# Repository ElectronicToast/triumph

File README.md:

Analog function generator project for EE 90 at Caltech

## Description

The Triumph Analog Function Generator is an analog function generator constructed for the Analog Electronics Project Laboratory (EE 90) capstone course at Caltech. It provides a single output channel on a 50 Ω impedance matched BNC connector. It is capable of producing sine, square, and triangle waveforms that vary in frequency over at least the range 10 Hz to 20 kHz, in addition to DC. The frequency may be adjusted through the combination of a frequency range select switch and a fine-adjustment knob on the top of the device. The output amplitude may be varied from zero up to 10 V (single-sided)  with a control knob. A second control knob allows the DC offset of the output to be varied. 

Power is supplied via 9 – 18 VDC input through a barrel jack connector on the rear of the device. A rocker switch near the power connector allows the device to be switched on and off.

A blue indicator LED on the front of the device indicates if the function generator is powered.

## Photos

## Design

An integrator with Schmitt feedback is used to generate a base triangle wave, which is passed to a Middlebrook-Richer JFET converter to create a sine wave and also a comparator to create a square wave. A positive feedback circuit associated to the comparator provides square wave duty cycle control. A final output stage provides amplitude and offset control. This general architecture achieves a good balance among simplicity, reliability, and performance.

The electronics were split among two PCBs: a main board with the function generator circuitry, and a power board that functions as a DC-DC converter supplying the former with a dual polarity power supply.

The electronics were designed with KiCad EDA v. 5.1.2. The `/triumph-main` directory contains files, documentation, and fabrication output for the main board, while the `/triumph-main-production` directory contains files reflecting post-fabrication design changes. The `/triumph-power` directory contains files for the power board.

The enclosure was designed with SolidWorks 2018, CorelDraw X7, and the [MakerCase](https://en.makercase.com/) box generator.

## Author
- Ray Sun - Undergraduate, Electrical Engineering, Caltech, Class of 2020

## Licensing
This project is released under the terms of the MIT License.

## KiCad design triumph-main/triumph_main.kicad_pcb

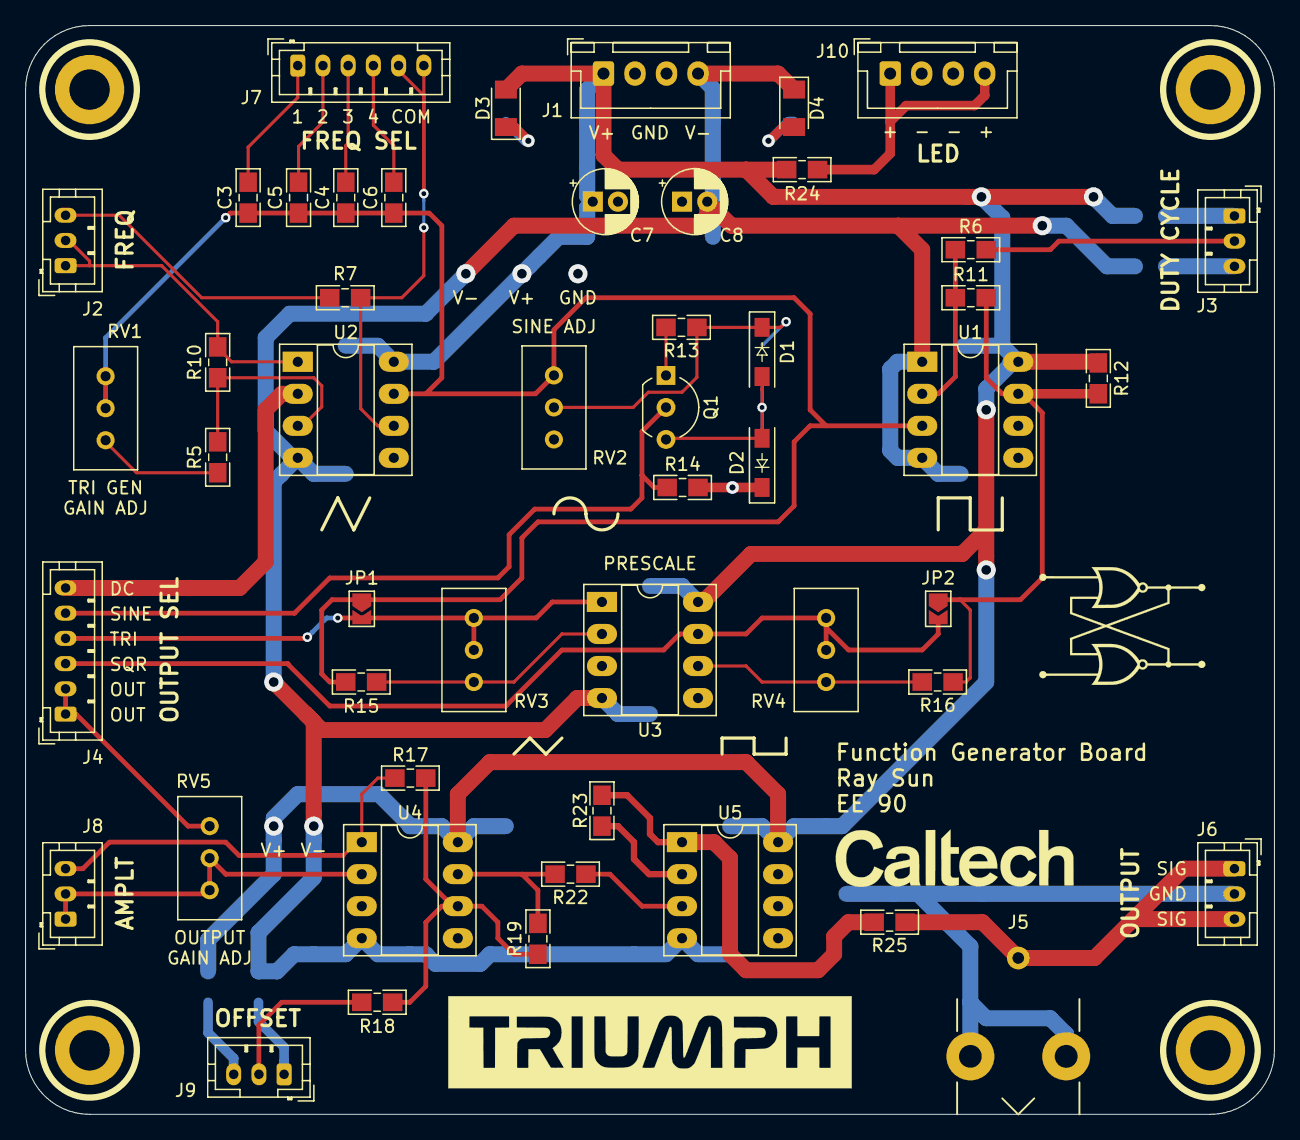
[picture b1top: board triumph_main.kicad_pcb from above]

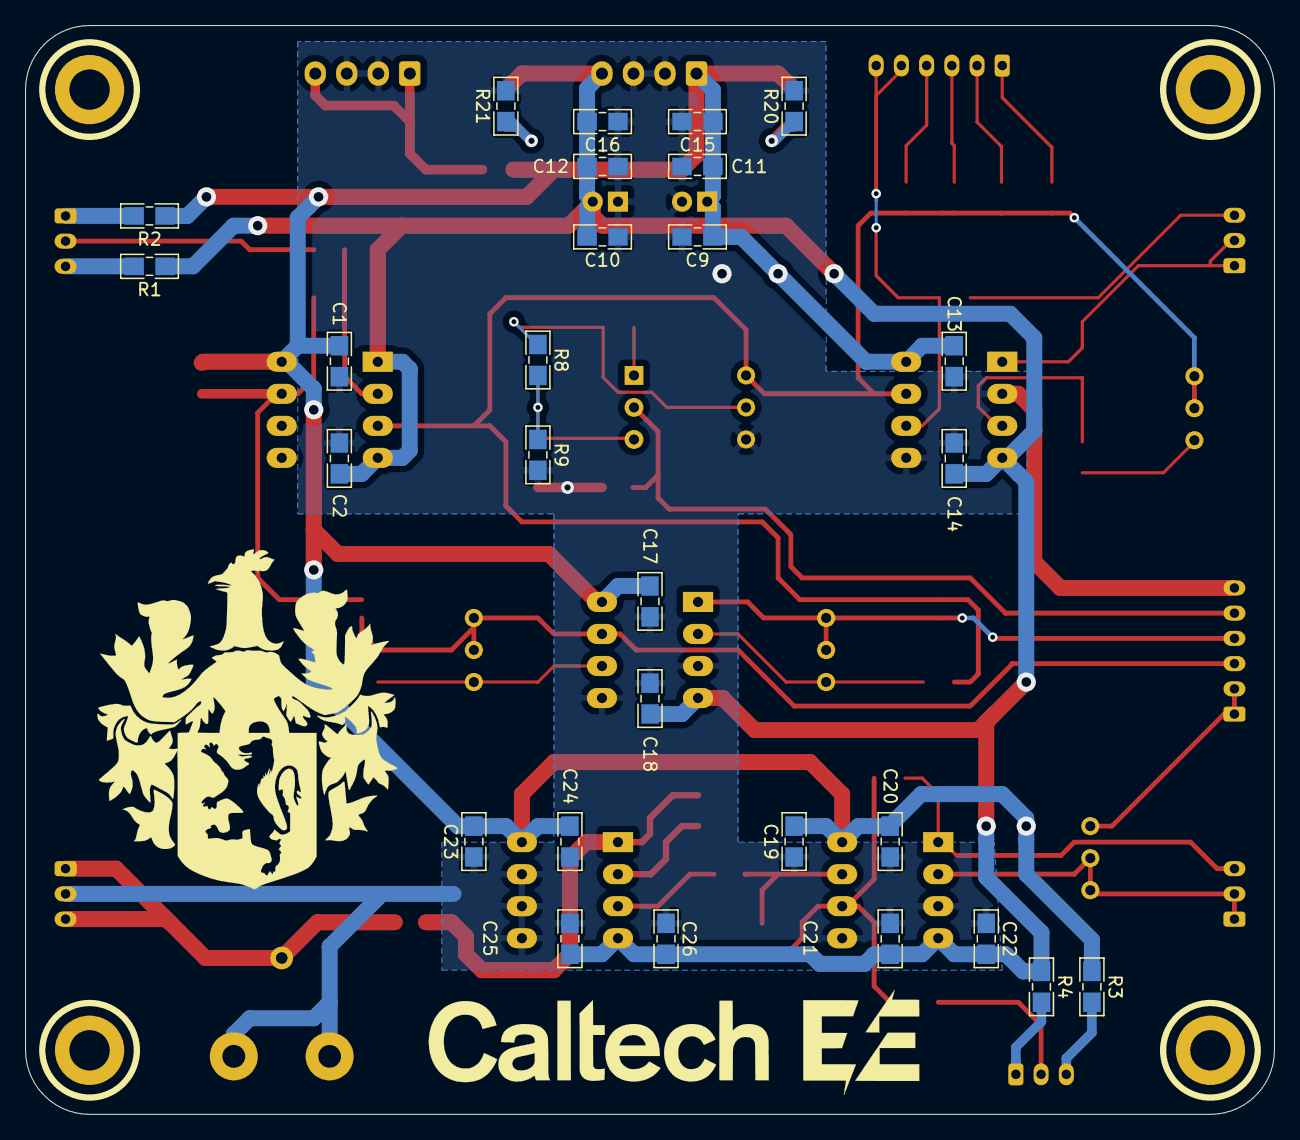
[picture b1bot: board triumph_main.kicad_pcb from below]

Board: 2 copper layers, 99.1 x 86.4 mm, 78 parts (28 on the bottom side), 41 nets.

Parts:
C1, C2, C4, C11, C12, C13, C14, C17, C18, C20, C21, C24, C25: 0.1uF; 0805_C_HandSoldering
C3, C19, C22, C23, C26: 10uF; 0805_C_HandSoldering
C5, C9, C10: 1uF; 0805_C_HandSoldering
C6: 10nF; 0805_C_HandSoldering
C7, C8: 10uF; CP_Radial_D5.0mm_P2.00mm
C15, C16: 0.01uF; 0805_C_HandSoldering
D1, D2: 1N4148; D_SOD-123_HandSoldering
D3, D4: BLUE; LED_1206_HandSoldering
J1, J10: JST_XH_vert_01x04; JST_XH_B4B-XH-A_1x04_P2.50mm_Vertical
J2, J3, J6, J8, J9: JST_PH_vert_01x03; JST_PH_B3B-PH-K_1x03_P2.00mm_Vertical
J4, J7: JST_PH_vert_01x06; JST_PH_B6B-PH-K_1x06_P2.00mm_Vertical
J5: Conn_BNC; Conn_BNC_73100-0154
JP1, JP2: SJ_OPEN; SolderJumper-2_P1.3mm_Open_TrianglePad1.0x1.5mm
Q1: J310; TO-92_Inline_Wide
R1, R2, R3, R4, R22, R23: 0; 0805_R_HandSoldering
R5, R17, R18, R19: 47K; 0805_R_HandSoldering
R6: 1K; 0805_R_HandSoldering
R7, R25: 50; 0805_R_HandSoldering
R8, R9, R10, R11: 100K; 0805_R_HandSoldering
R12: 5K; 0805_R_HandSoldering
R13, R14: 68; 0805_R_HandSoldering
R15, R16, R20, R21, R24: 10K; 0805_R_HandSoldering
RV1, RV2, RV3, RV4, RV5: 10K; Potentiometer_Bourns_3296W_Vertical
U1: LM211P; DIP-8_W7.62mm_Socket_LongPads
U2, U3, U4, U5: NE5532AP; DIP-8_W7.62mm_Socket_LongPads

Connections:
+12V: C1.1, C7.1, C9.1, C11.1, C13.2, C15.1, C17.2, C19.2, C20.2, C23.2, C24.2, D3.2, J1.1, R2.1, R3.1, R12.1, R24.1, U1.8, U2.8, U3.8, U4.8, U5.8
-12V: C2.1, C8.2, C10.2, C12.2, C14.2, C16.2, C18.2, C21.2, C22.2, C25.2, C26.2, D4.1, J1.4, R1.1, R4.1, U1.1, U1.4, U2.4, U3.4, U4.4, U5.4
/APL_1: J8.1, J8.2, RV5.2, RV5.3, U4.2
/APL_2: J8.3, R17.1, U4.1
/DC: J3.2, R6.1
/FC_1: C3.2, J7.1
/FC_2: C5.2, J7.2
/FC_3: C4.2, J7.3
/FC_4: C6.2, J7.4
/FC_COM: J7.5, J7.6, R7.1, U2.6
/FR_1: J2.1, J2.2, R10.2, U2.1
/FR_2: J2.3, R7.2
/OFFSET: J9.2, R18.1
/SIG_OUT: J5.1, J6.1, J6.3, R25.1
/SIG_PREOUT: J4.1, J4.2, RV5.1
/SIG_SIN: J4.5, Q1.2, R14.1
/SIG_SQR: J4.3, JP2.2, RV4.1, RV4.2, U3.7
/SIG_SQR_RAW: JP2.1, R11.2, R12.2, R16.1, U1.7
/SIG_TRI: J4.4, JP1.2, RV3.1, RV3.2, U3.1
/SIG_TRI_RAW: C3.1, C4.1, C5.1, C6.1, JP1.1, R15.1, RV1.1, RV1.2, RV2.1, U1.3, U2.7
GND: C1.2, C2.2, C7.2, C8.1, C9.2, C10.1, C11.2, C12.1, C13.1, C14.1, C15.2, C16.1, C17.1, C18.1, C19.1, C20.1, C21.1, C22.1, C23.1, C24.1, C25.1, C26.1, D2.1, J1.2, J1.3, J4.6, J5.2, J6.2, J10.2, J10.3, R9.2, R14.2, R20.2, R21.2, RV2.3, U2.2, U2.5, U3.3, U3.5, U4.3, U4.5, U5.5, U5.6, U5.7
unnamed: D1.1, R8.1, R13.1, RV2.2
unnamed: D1.2, D2.2, Q1.3, R8.2, R9.1
unnamed: D3.1, R20.1
unnamed: D4.2, R21.1
unnamed: J3.1, R2.2
unnamed: J3.3, R1.2
unnamed: J9.1, R4.2
unnamed: J9.3, R3.2
unnamed: J10.1, J10.4, R24.2
unnamed: Q1.1, R13.2
unnamed: R5.1, RV1.3
unnamed: R5.2, R10.1, U2.3
unnamed: R6.2, R11.1, U1.2
unnamed: R15.2, RV3.3, U3.2
unnamed: R16.2, RV4.3, U3.6
unnamed: R17.2, R18.2, R19.1, U4.6
unnamed: R19.2, R22.2, U4.7
unnamed: R22.1, U5.3
unnamed: R23.1, R25.2, U5.1
unnamed: R23.2, U5.2

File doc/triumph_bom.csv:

Date,5/19/2019,,,,,
,,,,,,
Power Board:,,,,,,
Component Count:,15,,,,,
Ref,Qnty,Value,Cmp name,Footprint,Description,Vendor
"C2, C1, ",2,47uF,CP_Small,Capacitor_THT:CP_Radial_D6.3mm_P2.50mm,"Polarized capacitor, small symbol",In House
"C4, C5, ",2,10uF,CP_Small,Capacitor_THT:CP_Radial_D5.0mm_P2.00mm,"Polarized capacitor, small symbol",In House
"C6, C7, ",2,1uF,C_Small,triumph:0805_C_HandSoldering,"Unpolarized capacitor, small symbol",Arrow
"C8, C9, C3, ",3,0.1uF,C_Small,triumph:0805_C_HandSoldering,"Unpolarized capacitor, small symbol",Arrow
"C10, C11, ",2,0.01uF,C_Small,triumph:0805_C_HandSoldering,"Unpolarized capacitor, small symbol",Arrow
"F1, ",1,MF-R050,Polyfuse_Small,Fuse:Fuse_Littelfuse_395Series,"Resettable fuse, polymeric positive temperature coefficient, small symbol",Arrow
"J2, J1, ",2,JST_XH_vert_01x04,Conn_01x04,Connector_JST:JST_XH_B4B-XH-A_1x04_P2.50mm_Vertical,"Generic connector, single row, 01x04, script generated (kicad-library-utils/schlib/autogen/connector/)",In House
"U1, ",1,RS-1212D,RS-1212D,triumph:RS-xxxxD,Dual +/-12V Regulated Converter,In House
,,,,,,
Main Board:,,,,,,
Component Count:,78,,,,,
Ref,Qnty,Value,Cmp name,Footprint,Description,Vendor
"C3, C22, C26, C19, C23, ",5,10uF,C_Small,triumph:0805_C_HandSoldering,"Unpolarized capacitor, small symbol",Arrow
"C5, C9, C10, ",3,1uF,C_Small,triumph:0805_C_HandSoldering,"Unpolarized capacitor, small symbol",Arrow
"C7, C8, ",2,10uF,CP_Small,Capacitor_THT:CP_Radial_D5.0mm_P2.00mm,"Polarized capacitor, small symbol",In House
"C15, C16, C6, ",3,0.01uF,C_Small,triumph:0805_C_HandSoldering,"Unpolarized capacitor, small symbol",Arrow
"C21, C20, C24, C25, C2, C1, C14, C13, C18, C17, C4, C11, C12, ",13,0.1uF,C_Small,triumph:0805_C_HandSoldering,"Unpolarized capacitor, small symbol",Arrow
"D2, D1, ",2,1N4148,D_Small_ALT,triumph:D_SOD-123_HandSoldering,"Diode, small symbol, filled shape",Arrow
"D3, D4, ",2,LED_B,LED_Small_ALT,triumph:LED_1206_HandSoldering,"Light emitting diode, small symbol, filled shape",Arrow
"J1, J10, ",2,JST_XH_vert_01x04,Conn_01x04,Connector_JST:JST_XH_B4B-XH-A_1x04_P2.50mm_Vertical,"Generic connector, single row, 01x04, script generated (kicad-library-utils/schlib/autogen/connector/)",In House
"J4, J7, ",2,JST_PH_vert_01x06,Conn_01x06,Connector_JST:JST_PH_B6B-PH-K_1x06_P2.00mm_Vertical,"Generic connector, single row, 01x06, script generated (kicad-library-utils/schlib/autogen/connector/)",In House
"J5, ",1,Molex_73100-0154,Conn_Coaxial,triumph:Conn_BNC_73100-0154,"coaxial connector (BNC, SMA, SMB, SMC, Cinch/RCA, ...)",Arrow
"J9, J8, J3, J2, J6, ",5,JST_PH_vert_01x03,Conn_01x03,Connector_JST:JST_PH_B3B-PH-K_1x03_P2.00mm_Vertical,"Generic connector, single row, 01x03, script generated (kicad-library-utils/schlib/autogen/connector/)",In House
"JP1, JP2, ",2,SJ_OPEN,SolderJumper_2_Open,Jumper:SolderJumper-2_P1.3mm_Open_TrianglePad1.0x1.5mm,"Solder Jumper, 2-pole, open",N/A
"Q1, ",1,J310,Q_NJFET_DSG,Package_TO_SOT_THT:TO-92_Inline_Wide,"N-JFET transistor, drain/source/gate",In House
"R2, R1, R4, R3, R22, R23, ",6,0,R_Small_US,triumph:0805_R_HandSoldering,"Resistor, small US symbol",G. G.
"R6, ",1,1K,R_Small_US,triumph:0805_R_HandSoldering,"Resistor, small US symbol",In House
"R8, R9, R10, R11, ",4,100K,R_Small_US,triumph:0805_R_HandSoldering,"Resistor, small US symbol",Arrow
"R12, ",1,5K,R_Small_US,triumph:0805_R_HandSoldering,"Resistor, small US symbol",Arrow
"R14, R13, ",2,68,R_Small_US,triumph:0805_R_HandSoldering,"Resistor, small US symbol",Arrow
"R19, R17, R18, R5, ",4,47K,R_Small_US,triumph:0805_R_HandSoldering,"Resistor, small US symbol",Arrow
"R24, R15, R16, R20, R21, ",5,10K,R_Small_US,triumph:0805_R_HandSoldering,"Resistor, small US symbol",In House
"R25, R7, ",2,50,R_Small_US,triumph:0805_R_HandSoldering,"Resistor, small US symbol",Arrow
"RV2, RV1, RV3, RV4, ",4,10K,R_POT_US,Potentiometer_THT:Potentiometer_Bourns_3296W_Vertical,"Potentiometer, US symbol",Arrow
"RV5, ",1,200K,R_POT_US,Potentiometer_THT:Potentiometer_Bourns_3296W_Vertical,"Potentiometer, US symbol",Digi-Key
"U1, ",1,LM211P,LM311,Package_DIP:DIP-8_W7.62mm_Socket_LongPads,"Voltage Comparator, DIP-8/SOIC-8/SSOP-8",In House
"U4, U5, U2, U3, ",4,AD826,TL072,Package_DIP:DIP-8_W7.62mm_Socket_LongPads,"Dual Low-Noise JFET-Input Operational Amplifiers, DIP-8/SOIC-8",In House
N/A,5,DIP-8 socket,,,,In House

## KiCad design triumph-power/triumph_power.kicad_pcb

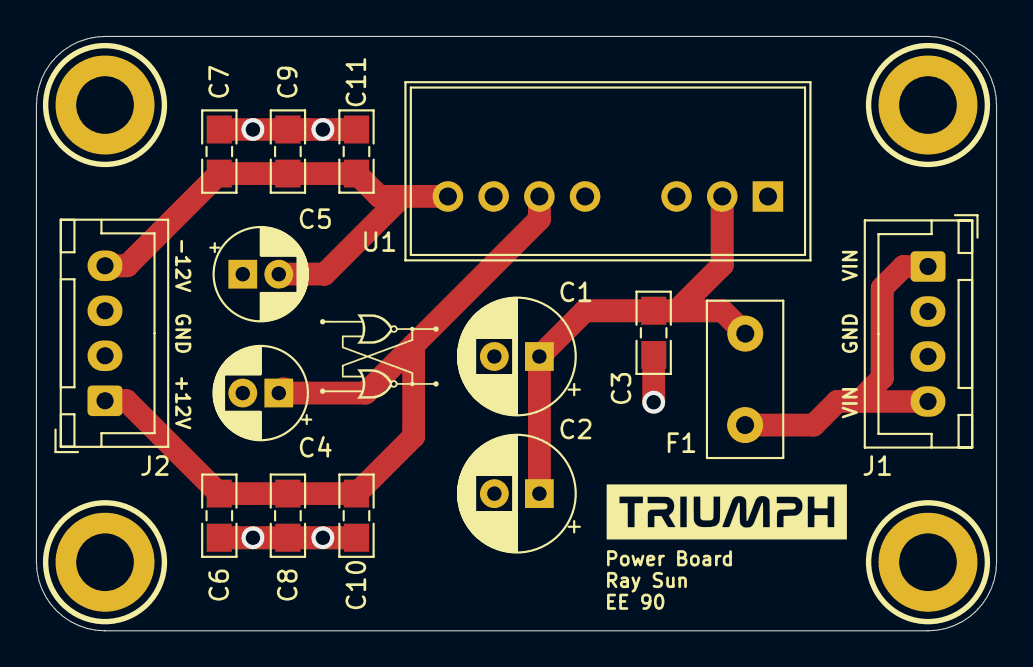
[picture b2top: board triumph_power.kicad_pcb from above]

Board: 2 copper layers, 53.3 x 33.0 mm, 15 parts (0 on the bottom side), 6 nets.

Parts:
C1, C2: 47uF; CP_Radial_D6.3mm_P2.50mm
C3, C8, C9: 0.1uF; 0805_C_HandSoldering
C4, C5: 10uF; CP_Radial_D5.0mm_P2.00mm
C6, C7: 1uF; 0805_C_HandSoldering
C10, C11: 0.01uF; 0805_C_HandSoldering
F1: MF-R050; Fuse_Littelfuse_395Series
J1, J2: JST_XH_vert_01x04; JST_XH_B4B-XH-A_1x04_P2.50mm_Vertical
U1: RS-1212D; RS-xxxxD

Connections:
+12V: C4.1, C6.1, C8.1, C10.1, J2.1, U1.6
-12V: C5.2, C7.2, C9.2, C11.2, J2.4, U1.8
GND: C4.2, C5.1, C6.2, C7.1, C8.2, C9.1, C10.2, C11.1, J2.2, J2.3, U1.7
GNDREF: C1.2, C2.2, C3.2, J1.2, J1.3, U1.1
unnamed: C1.1, C2.1, C3.1, F1.2, U1.2
VCC: F1.1, J1.1, J1.4

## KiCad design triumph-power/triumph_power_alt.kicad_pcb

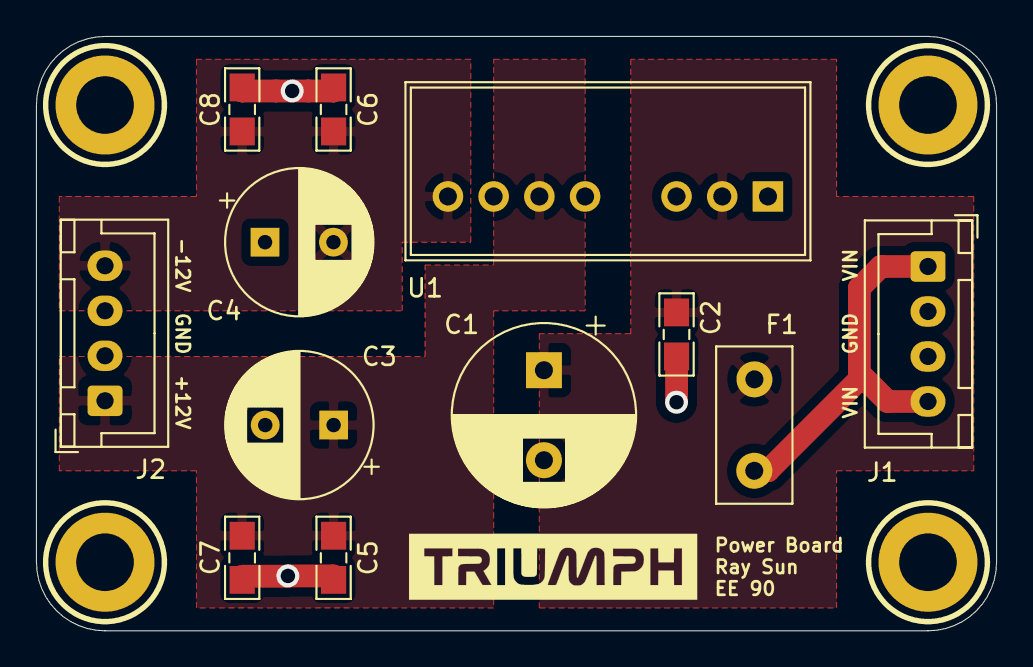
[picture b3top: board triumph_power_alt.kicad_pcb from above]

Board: 2 copper layers, 53.3 x 33.0 mm, 12 parts (0 on the bottom side), 6 nets.

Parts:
C1: 47uF; CP_Radial_D10.0mm_P5.00mm
C2, C5, C6: 0.1uF; 0805_C_HandSoldering
C3, C4: 10uF; CP_Radial_D8.0mm_P3.80mm
C7, C8: 0.01uF; 0805_C_HandSoldering
F1: MF-R050; Fuse_Littelfuse_395Series
J1, J2: JST_XH_vert_01x04; JST_XH_B4B-XH-A_1x04_P2.50mm_Vertical
U1: RS-1212D; RS-xxxxD

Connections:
+12V: C3.1, C5.1, C7.1, J2.1, U1.6
-12V: C4.2, C6.2, C8.2, J2.4, U1.8
GND: C3.2, C4.1, C5.2, C6.1, C7.2, C8.1, J2.2, J2.3, U1.7
GNDREF: C1.2, C2.2, J1.2, J1.3, U1.1
unnamed: C1.1, C2.1, F1.2, U1.2
VCC: F1.1, J1.1, J1.4

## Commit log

2019-04-12 Add power board files
2019-04-15 Generate main board files
2019-04-15 Change to dual transformers
2019-04-17 Add some power components
2019-04-17 Spec potentiometer connectors
2019-04-21 Design output stage
2019-04-22 Complete initial schematic
2019-04-22 Annotate schematic
2019-04-22 Add additional annotation
2019-04-22 Update Wien bridge cap values
2019-04-23 Add project logos
2019-04-25 Add title block images
2019-04-25 Fix inane KiCad 5.1.0 labels bug
2019-04-25 Add more input decoupling
2019-04-25 Make schematic version without AC DC converter board
2019-04-25 Add DC-DC converter
2019-04-30 Add PTC
2019-05-02 Migrate to square-triangle generation, sine shaping
2019-05-02 Make pot pinout standard orientation agnostic
2019-05-05 Update output matching, Middlebrook
2019-05-05 Update current wave generation design
2019-05-05 Remove board LEDs
2019-05-05 Make output select symmetric
2019-05-05 Add comparator for DC control
2019-05-05 Remove protection resistor from gain stage
2019-05-05 Remove pulldown
2019-05-05 Update labels
2019-05-05 Respec power connector
2019-05-10 Refactor into two separate boards
2019-05-10 Assign 4 pin XH footprint
2019-05-10 Add preliminary power board
2019-05-10 Add trimpots and auxiliary power connector
2019-05-11 Add 0 ohm shunts
2019-05-11 Update square generator
2019-05-12 Update to breadboard prototype
2019-05-12 Generate preliminary schematic print
2019-05-12 Add RS-1212D symbol and footprint
2019-05-12 Route power board
2019-05-12 Make fat 0805 footprints
2019-05-12 Add more logo images
2019-05-12 Add a prodigious quantity of PCB graphics
2019-05-12 Add alternative PCB based on planes
2019-05-12 Replace input resistor on output gain stage with trimpot
2019-05-12 Assign provisional footprints for BNC and tantalum caps
2019-05-12 Replace 0805 footprints with custom ones
2019-05-12 Replace LM211 footprint with DIP8 socket
2019-05-12 Begin layout
2019-05-12 Continue placement
2019-05-12 Copy schematic for alternative power board
2019-05-13 Generate preliminary documentation
2019-05-13 Remove alternative power board
2019-05-13 Add additional power filtering caps and update electrolytic cap footprints
2019-05-13 Add and rename some logos
2019-05-13 Reroute power board
2019-05-13 Generate gerbers
2019-05-13 Update schematic plot
2019-05-13 Add zip for FreeDFM
2019-05-13 Remove paste gerbers
2019-05-13 Add board dimension markers
2019-05-13 Change dimensions to inches
2019-05-13 Add large SOD-123 footprint
2019-05-13 Add cap bank
2019-05-13 Correct tantalum orientation
2019-05-14 Determine board edge
2019-05-14 Determine board outline
2019-05-14 Add BNC connector footprint
2019-05-14 Modify orientation
2019-05-14 Begin routing
2019-05-14 Add Ruddock crest silkscreen logos
2019-05-14 Make cosmetic edits
2019-05-14 Add more cosmetics
2019-05-14 Finish routing
2019-05-14 Add more labels
2019-05-14 Add additional logo footprints
2019-05-14 Add missing conector labels
2019-05-14 Make some traces thicker, 50 mil power
2019-05-14 Update pdf
2019-05-14 Make thicker intermediate signal traces, more labels
2019-05-14 Remove via tenting
2019-05-15 Add onboard power LEDs
2019-05-15 Regenerate pdf
2019-05-15 Correct triangle wave opamp orientation
2019-05-15 Remove archive
2019-05-15 Generate first version documentation
2019-05-15 Remove drill files from documentation
2019-05-19 Edit some component fields to reflect values for production
2019-05-19 Rename 10nF to 0.01uF
2019-05-19 Generate letter size fabrication schematic and BOMs
2019-05-19 Make combined BOM
2019-05-20 Order parts
2019-06-03 Add schematic to represent actual production values used
2019-06-13 Generate more documentation
2019-06-13 Add more documentation
2019-06-13 Add enclosure fabrication file
2019-06-22 Add completed project photos
